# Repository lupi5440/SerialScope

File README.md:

# 🔬 SerialScope — Sistema de Análisis de Protocolos

**SerialScope** es un ecosistema de hardware y software diseñado para la visualización, análisis y emulación de protocolos de comunicación serial (**UART, I²C y SPI**). Esta introduce capacidades de **Maestro Activo**, permitiendo interactuar con sensores reales (como el MAX6675) y emular dispositivos complejos directamente desde una interfaz web .

---

## 🏗️ Arquitectura del Sistema (V3)

El sistema utiliza una arquitectura híbrida para garantizar que la visualización no afecte el rendimiento del bus físico.

```mermaid
graph TD
    subgraph Dashboard
        WEB[Interfaz Web - Vite/React]
    end

    subgraph Hardware_Cores
        VIS[ESP32 Visualizador]
        MST[ESP32 Maestro de Pruebas]
        SLV[ESP32 Esclavo de Pruebas]
    end

    WEB -- "WiFi (WebSockets)" --> VIS
    WEB -- "Bluetooth (BLE)" --> MST
    WEB -- "Bluetooth (BLE)" --> SLV

    MST -- "Bus Físico (I2C/SPI/UART)" --> VIS
    VIS -- "MISO/SDA/RX" --> WEB
    MST -- "UART" --> SLV
```

### 🛰️ Componentes Hardware
| Componente | Conectividad | Propósito |
|---|---|---|
| **Visualizador (Sniffer/Master)** | **WiFi** | Analizador lógico pasivo o **Maestro SPI/I2C** directo para leer sensores. |
| **Maestro (Emulador)** | **BLE** | Genera tráfico controlado, emula sensores (BMP180/TMP102) y controla periféricos (TFT). |
| **Esclavo (Receptor)** | **BLE** | Extremo final de la ráfaga UART para pruebas de integridad y bidireccionalidad. |

---

## 🚀 Capacidades 

### ⚡ Protocolo SPI (Serial Peripheral Interface)
- **Sniffing Pasivo:** Monitoreo en tiempo real de ráfagas MOSI/MISO sincronizadas con el reloj (SCK).
- **Maestro Activo:** Capacidad de generar el reloj (SCK) y CS para leer sensores (ej. MAX6675) y controlar periféricos (TFT).
- **Emulación de Sensor:** El visualizador puede actuar como Esclavo para responder a otros maestros con datos HEX personalizados.

### 🧩 Protocolo I²C (Inter-Integrated Circuit)
- **Auto-Sniffing:** Captura automática de direcciones y registros mediante interrupciones de hardware.
- **Maestro Activo:** Capacidad de lectura y escritura directa sobre dispositivos esclavos desde la interfaz web.
- **Emulación de Sensor:** Simulación de una memoria de registros (256 bytes) para pruebas de integración.

### 📡 Protocolo UART (Comunicación Serial)
- **Sniffing Pasivo:** Intercepción de mensajes entre dos dispositivos (Proxy transparente).
- **Maestro Activo:** Generación de mensajes seriales con baudrates configurables (9600 a 115200).
- **Emulación:** Respuesta automática controlada para validación de enlaces bidireccionales.

---

## 🛠️ Instalación y Uso

### Interfaz Web
La interfaz utiliza **Vite** para una experiencia rápida y un diseño basado en **Glassmorphism**.
```bash
cd WebInterface
npm install
npm run dev
```
Accede a `http://localhost:5173` para entrar al panel de control.

### Firmware (ESP32)
Es **CRÍTICO** utilizar el **ESP32 Arduino Core 3.0.0+** debido al uso de las APIs de PWM (`ledcAttach`). Puedes encontrar más información sobre este cambio [aquí](https://docs.espressif.com/projects/arduino-esp32/en/latest/api/ledc.html).

**Librerías Requeridas:**
- `Adafruit GFX Library` (v1.11.9)
- `Adafruit ST7735 and ST7789 Library` (v1.10.3)
- `MAX6675 library` (v1.1.2)
- [AsyncTCP (Fork de mathieucarbou)](https://github.com/mathieucarbou/AsyncTCP)
- [ESPAsyncWebServer (Fork de mathieucarbou)](https://github.com/mathieucarbou/ESPAsyncWebServer)

**Software de Desarrollo:**
- **Arduino IDE**: 2.3.2+ o VS Code + PlatformIO.
- **ESP32 Arduino Core**: 3.0.0 o superior.

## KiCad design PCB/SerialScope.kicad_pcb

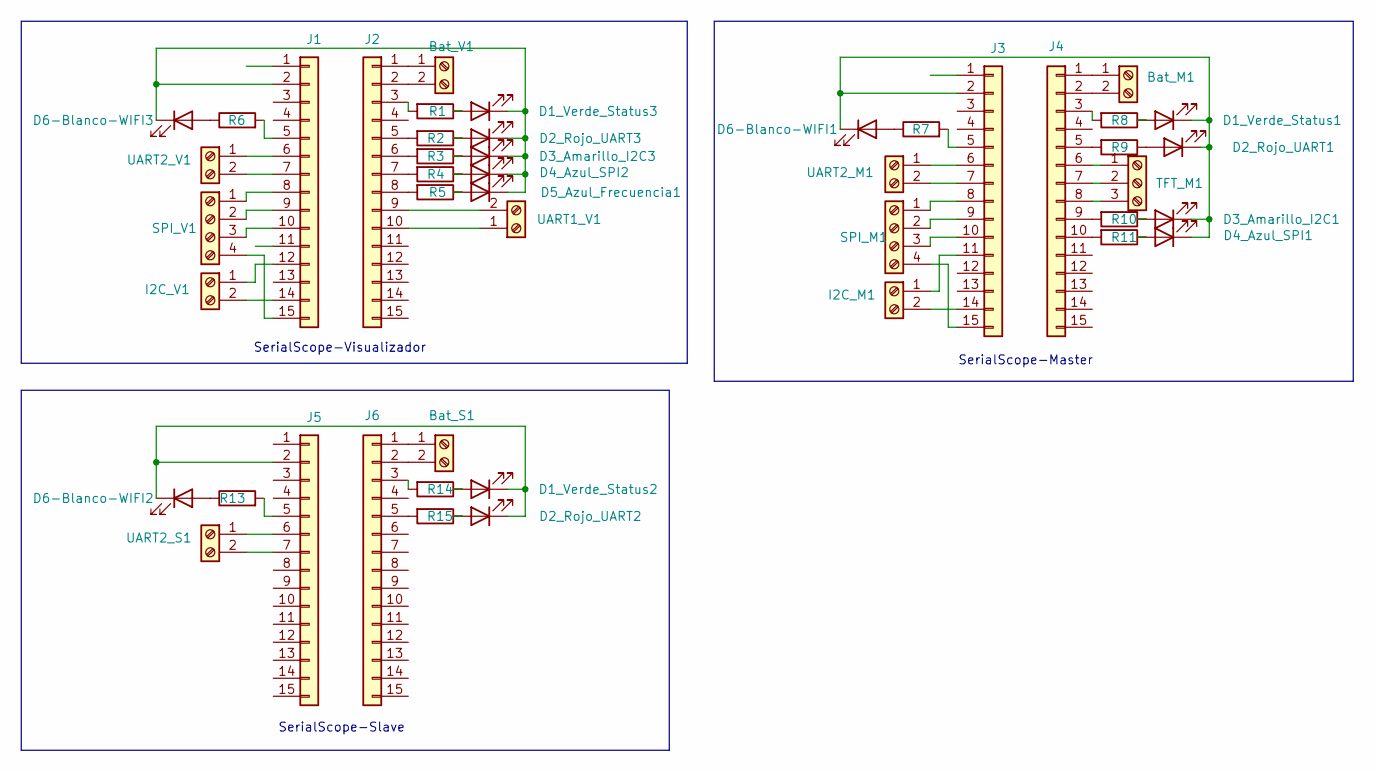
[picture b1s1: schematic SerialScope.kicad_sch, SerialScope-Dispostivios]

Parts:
Bat_M1: Screw_Terminal_01x02; TerminalBlock_MaiXu_MX126-5.0-02P_1x02_P5.00mm
Bat_S1: Screw_Terminal_01x02; TerminalBlock_MaiXu_MX126-5.0-02P_1x02_P5.00mm
Bat_V1: Screw_Terminal_01x02; TerminalBlock_MaiXu_MX126-5.0-02P_1x02_P5.00mm
D1_Verde_Status1, D1_Verde_Status2, D1_Verde_Status3, D2_Rojo_UART1, D2_Rojo_UART2, D2_Rojo_UART3, D3_Amarillo_I2C1, D3_Amarillo_I2C3, D4_Azul_SPI1, D4_Azul_SPI2, D5_Azul_Frecuencia1, D6-Blanco-WIFI1, D6-Blanco-WIFI2, D6-Blanco-WIFI3: LED; LED_D5.0mm
I2C_M1, I2C_V1: Screw_Terminal_01x02; TerminalBlock_MaiXu_MX126-5.0-02P_1x02_P5.00mm
J1, J2, J3, J4, J5, J6: Conn_01x15; PinSocket_1x15_P2.54mm_Vertical
R1, R2, R3, R4, R5, R6, R7, R8, R9, R10, R11, R13, R14, R15: 330; R_Axial_DIN0207_L6.3mm_D2.5mm_P10.16mm_Horizontal
SPI_M1: Screw_Terminal_01x04; TerminalBlock_MaiXu_MX126-5.0-04P_1x04_P5.00mm
SPI_V1: Screw_Terminal_01x04; TerminalBlock_MaiXu_MX126-5.0-04P_1x04_P5.00mm
TFT_M1: Screw_Terminal_01x03; TerminalBlock_MaiXu_MX126-5.0-03P_1x03_P5.00mm
UART1_V1, UART2_M1, UART2_S1, UART2_V1: Screw_Terminal_01x02; TerminalBlock_MaiXu_MX126-5.0-02P_1x02_P5.00mm

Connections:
unnamed: Bat_M1.1, J4.1
unnamed: Bat_M1.2, J4.2
unnamed: Bat_S1.1, J6.1
unnamed: Bat_S1.2, J6.2
unnamed: Bat_V1.1, J2.1
unnamed: Bat_V1.2, J2.2
unnamed: D1_Verde_Status1.2 (A), R8.1
unnamed: D1_Verde_Status1.1 (K), D2_Rojo_UART1.1 (K), D3_Amarillo_I2C1.1 (K), D4_Azul_SPI1.1 (K), D6-Blanco-WIFI1.1 (K), J3.2
unnamed: D1_Verde_Status2.2 (A), R14.1
unnamed: D1_Verde_Status2.1 (K), D2_Rojo_UART2.1 (K), D6-Blanco-WIFI2.1 (K), J5.2
unnamed: D1_Verde_Status3.2 (A), R1.1
unnamed: D1_Verde_Status3.1 (K), D2_Rojo_UART3.1 (K), D3_Amarillo_I2C3.1 (K), D4_Azul_SPI2.1 (K), D5_Azul_Frecuencia1.1 (K), D6-Blanco-WIFI3.1 (K), J1.2
unnamed: D2_Rojo_UART1.2 (A), R9.1
unnamed: D2_Rojo_UART2.2 (A), R15.1
unnamed: D2_Rojo_UART3.2 (A), R2.1
unnamed: D3_Amarillo_I2C1.2 (A), R10.1
unnamed: D3_Amarillo_I2C3.2 (A), R3.1
unnamed: D4_Azul_SPI1.2 (A), R11.1
unnamed: D4_Azul_SPI2.2 (A), R4.1
unnamed: D5_Azul_Frecuencia1.2 (A), R5.1
unnamed: D6-Blanco-WIFI1.2 (A), R7.1
unnamed: D6-Blanco-WIFI2.2 (A), R13.1
unnamed: D6-Blanco-WIFI3.2 (A), R6.1
unnamed: I2C_M1.1, J3.11
unnamed: I2C_M1.2, J3.14
unnamed: I2C_V1.1, J1.12
unnamed: I2C_V1.2, J1.14
unnamed: J1.5, R6.2
unnamed: J1.6, UART2_V1.1
unnamed: J1.7, UART2_V1.2
unnamed: J1.8, SPI_V1.1
unnamed: J1.9, SPI_V1.2
unnamed: J1.10, SPI_V1.3
unnamed: J1.15, SPI_V1.4
unnamed: J2.3, R1.2
unnamed: J2.5, R2.2
unnamed: J2.6, R3.2
unnamed: J2.7, R4.2
unnamed: J2.8, R5.2
unnamed: J2.9, UART1_V1.2
unnamed: J2.10, UART1_V1.1
unnamed: J3.5, R7.2
unnamed: J3.6, UART2_M1.1
unnamed: J3.7, UART2_M1.2
unnamed: J3.8, SPI_M1.1
unnamed: J3.9, SPI_M1.2
unnamed: J3.10, SPI_M1.3
unnamed: J3.15, SPI_M1.4
unnamed: J4.3, R8.2
unnamed: J4.5, R9.2
unnamed: J4.6, TFT_M1.1
unnamed: J4.7, TFT_M1.2
unnamed: J4.8, TFT_M1.3
unnamed: J4.9, R10.2
unnamed: J4.10, R11.2
unnamed: J5.5, R13.2
unnamed: J5.6, UART2_S1.1
unnamed: J5.7, UART2_S1.2
unnamed: J6.3, R14.2
unnamed: J6.5, R15.2

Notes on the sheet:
SerialScope-Slave
SerialScope-Visualizador
SerialScope-Master

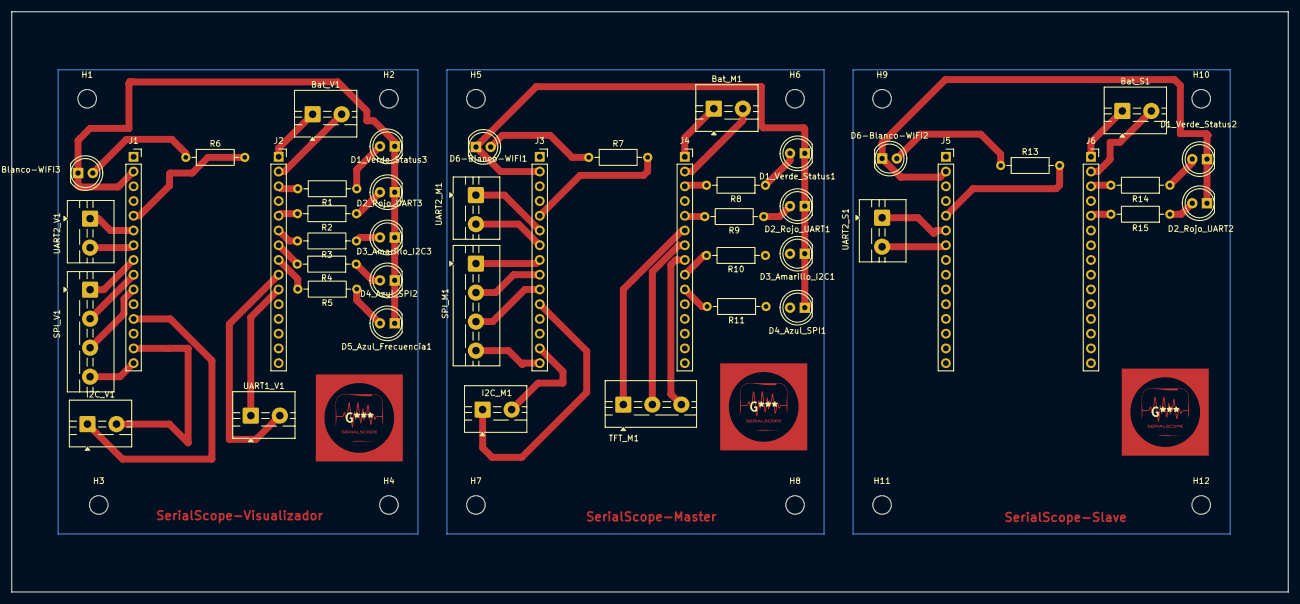
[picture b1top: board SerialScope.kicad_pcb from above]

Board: 2 copper layers, 220.0 x 100.0 mm, 58 parts (0 on the bottom side), 60 nets.

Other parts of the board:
H1, H2, H3, H4, H5, H6, H7, H8, H9, H10, H11, H12: MountingHole_3.2mm_M3

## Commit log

2026-05-07 SerialScope
2026-05-07 Actualizacion del readme
2026-05-07 archivo para despliege en githubpages
2026-05-07 Actualizacion porque no encontraba el package-lock.json
2026-05-07 Cambio de base en vite para que al subir si encuentre bien los enlaces a las paginas
2026-05-07 correcion al script de header
2026-05-10 Cambio de pines para facilitar conexion y mejorar velocidad
2026-05-11 Mejoras de salud y interfaz mas amigable
2026-05-12 Modificacion interfaz y funciones
2026-05-12 Modificaciones pwa , colores interfaz actualizada, funcionamiento de los puertos
2026-05-12 Organizacion del codigo visualizador y cambio de variable de comando por una cola xQue para que no haya condicion de carrera entre el hilo 1 (wifi) y el hilo 2 (loop)
2026-05-12 Cambio de string de buffer de UART a arreglos fijos , para evitar que se creen string temporales y sobrecargen la ram
2026-05-12 Solucion a problema de perdida de paquetes por ISP , y alerta cuando es necesario descartar datos de cola de paquetes a enviar a ws por diferentcia de de vleocidad entre sniffing y posibilidad que en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
2026-05-12 Recerva de memoria para i2c y spi en snifing para evitar que llege muy rapido y llene directamente la ram por la cache que teniamos
2026-05-12 Anteriormente en el loop principal aunque no estaba seleccionado el protocolo hacea sniffing de los 3 i2c,spi,uart, sin embargo como en configuracion haciamos que solo se enviaran cuando el protocolo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
2026-05-12 borrado de parseo de parametros mal echo que teniamos en js entre diversas versiones de la interfaz
2026-05-13 Implementacion de I2C y SPi en dos formas , modo maestro y modo esclavo simulando ser un sensor , actualmetne esta la interfaz y logica en el visualizador , pero no se han echo pruebas
2026-05-13 Limpieza jscript para pruebas
2026-05-14 Quitar modo 1mhz en i2c y correccion de comportamiento de led de status cuando habia un error
2026-05-14 Agregar heartbeat a conexion wifi y ble , correccion problema spi , que cambio enter dispositivos , la libreria de uno bloqueaba a la de otro entonces solo funciona el primero que configurara, prueba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
2026-05-14 Funcionamiento de todos los modos de los 3 protocolos , falta depurar hacer bien comentarios y organizar pero parece que es la ultima version en cuanto funcionalidad
2026-05-15 Correcciones para calidad de codigo , y mejorar en strings a printf para evitar saturacion de ram , asi mismo normalizacion de valores hardcodeados a su variables para futuro modificaciones
2026-05-15 Carpeta de firmware completa y funcional para documentar
2026-05-15 Borrar comentarios inecesarios
2026-05-15 Actualizacion del readme con la nueva version
2026-05-16 Subida de archivos para PCB
2026-05-17 Correccion a manejo de strings , a paso a estandar de arreglos para arduino
    Implementacion de canal dinamico para wifi para menor ruido
    Ping ahora muestra la latencia en la comunicacion
    Por cuestiones de pegado y borrado la funcion de spi slave y master estaban duplicadas , se quitaron y pusieron bien ya que las dos hacian cosas a mitades
2026-05-19 Modificacion pcb , 2 mm extras de separacion entre las hileras de pines para esp32
2026-05-19 Actualizacion medidas , correcciones de medidas
2026-05-21 ACTUALIZACION SPI CON LEYENDA SPI
2026-05-21 CORREXION DE LEYENDAS EN EL SPI
2026-05-22 Correcion a titulos para quitar lo del rs232
2026-05-22 correccion de videos del index
2026-06-04 Correccion comentarios
